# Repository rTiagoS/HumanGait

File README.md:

## "Classificação de Marcha Anômala utilizando técnicas de Machine Learning e Sensores Embarcados."

### Publicações

Para mais detalhes, verifique nosso artigo: https://arxiv.org/abs/2110.06139

Caso nosso dataset seja utilizado, por favor, nos cite utilizando a seguinte referência: &nbsp;
```
@misc{sa2021classification,
      title={Classification of anomalous gait using Machine Learning techniques and embedded sensors}, 
      author={T. R. D. Sa and C. M. S. Figueiredo},
      year={2021},
      eprint={2110.06139},
      archivePrefix={arXiv},
      primaryClass={eess.SP}
}
```

Link para o dataset: https://drive.google.com/drive/folders/1B0GRPU912k93h7YRrBrzX0vYdbw2wq_Z?usp=sharing

##### Este repositório, em síntese, viabiliza o acesso aos três módulos que implementam o projeto proposto. Os módulos são:

**1. Módulo da Aplicação Embarcada**;
   * Modelagem do esquemático e layout do hardware embarcado;
   * Integração do sensor MPU-6050 ao microcontrolador ESP32 DevKit C;
   * Integração dos dados coletados para um servidor Broker MQTT (Internet das Coisas);
  
  Tecnologias utilizadas:
   * Linguagens de programação C e C++ (implementação do software embarcado);
   * KiCAD para modelagem da PCB;
  
**2. Módulo da Aplicação Web**;
   * Implementação de uma interface para inserção de dados;
   * Integração ao ESP32 DevKit C e servidor Broker MQTT para testes de conexão;
   * Rotulação automática dos dados coletados para alimentar o dataset;
  
  Tecnologias utilizadas: 
  - Servidor Linux (Ubuntu 20.04) hospedando Node-RED e um servidor Broker MQTT Eclipse Mosquitto.
  
**3. Módulo da Aplicação IA**;
   * Implementação de diferentes modelos baseados em Machine Learning com a biblioteca scikit learn;
   * Implementação de diferentes modelos baseados em arquiteturas de Deep Learning com as bibliotecas Keras e Tensorflow;
  
  Tecnologias utilizadas:
   * Servidor Linux com GPU para treinamento de modelos de Deep Learning e Machine Learning;
   * Linguagem de programação Python para implementação dos modelos IA e rotinas de rotulagem automática do dataset;

 Para cada módulo, há um diretório com o respectivo nome de referência. Neles há os arquivos de implementação e entre outros detalhes.

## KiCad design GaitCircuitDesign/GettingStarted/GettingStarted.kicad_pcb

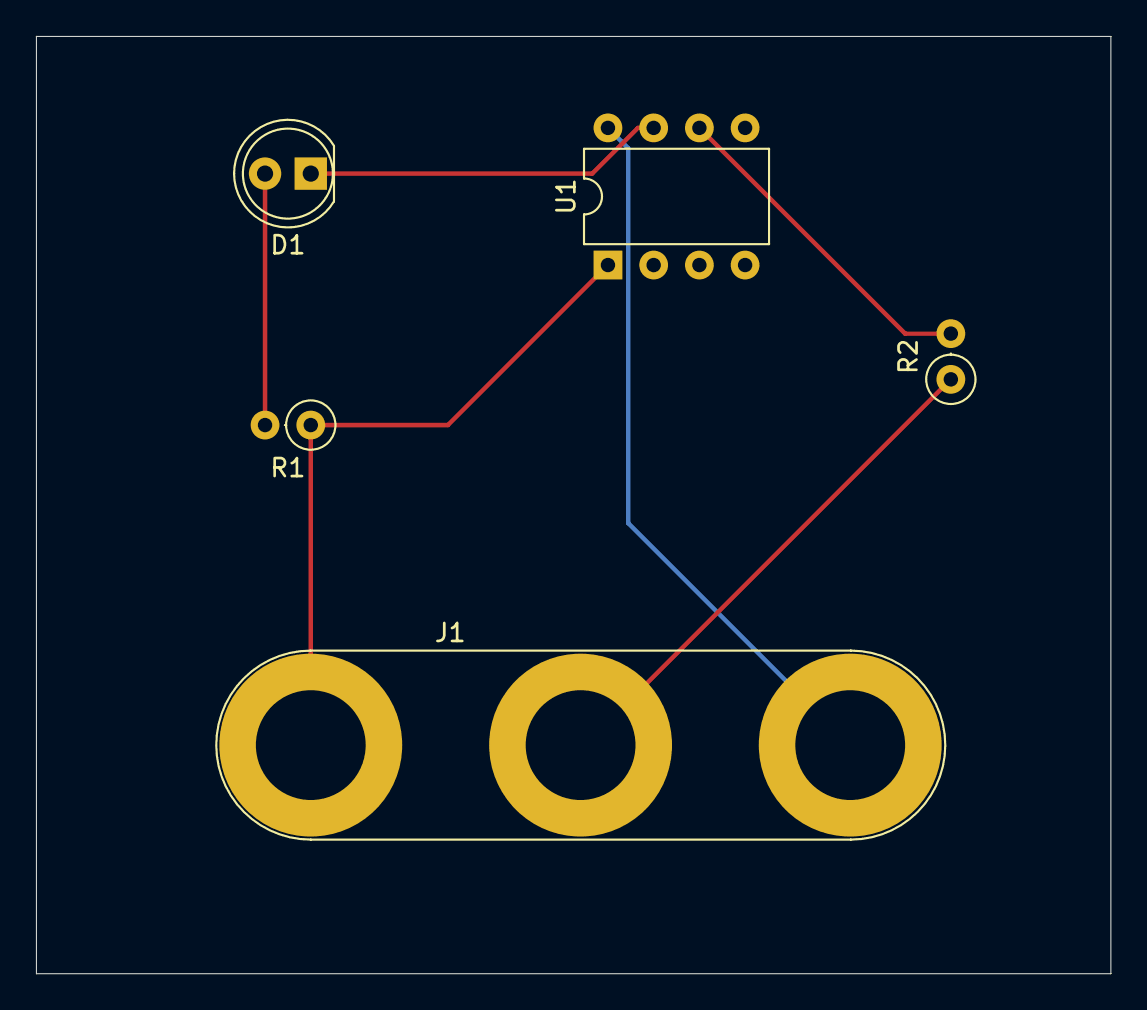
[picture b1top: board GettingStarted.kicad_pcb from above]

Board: 2 copper layers, 59.7 x 52.1 mm, 5 parts (0 on the bottom side), 6 nets.

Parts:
D1: LED; LED_D5.0mm
J1: MYCONN3; Banana_Jack_3Pin
R1: 1k; R_Axial_DIN0207_L6.3mm_D2.5mm_P2.54mm_Vertical
R2: 100; R_Axial_DIN0207_L6.3mm_D2.5mm_P2.54mm_Vertical
U1: PIC12C508A-ISN; DIP-8_W7.62mm

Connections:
/INPUT: R2.2, U1.6
/INPUTtoR: J1.2, R2.1
/LEDtoR: D1.2, R1.2
/uCtoLED: D1.1, U1.7
GND: J1.3, U1.8
VCC: J1.1, R1.1, U1.1

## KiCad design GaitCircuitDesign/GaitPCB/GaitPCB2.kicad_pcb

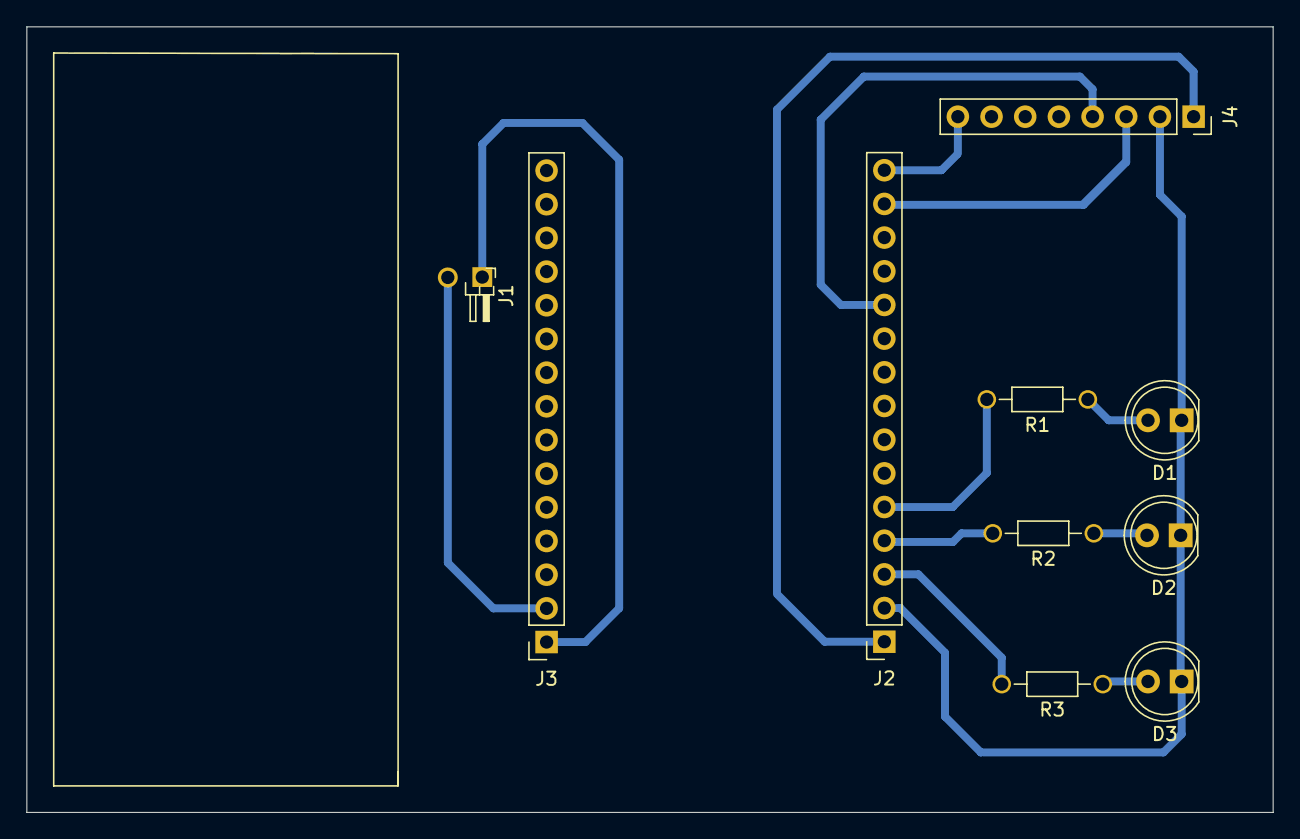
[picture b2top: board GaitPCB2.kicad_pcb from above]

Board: 2 copper layers, 94.0 x 59.2 mm, 10 parts (0 on the bottom side), 12 nets.

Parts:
D1, D2, D3: LED; LED_D5.0mm
J1: Conn_01x02_Male; PinHeader_1x02_P1.00mm_Horizontal
J2: Conn_01x15_Female_MPU; PinSocket_1x15_P2.54mm_Vertical
J3: Conn_01x15_Female; PinSocket_1x15_P2.54mm_Vertical
J4: Conn_01x08_Female; PinSocket_1x08_P2.54mm_Vertical
R1, R2, R3: R; R_Axial_DIN0204_L3.6mm_D1.6mm_P7.62mm_Horizontal

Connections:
+3V3: J2.1, J4.1
GND: D1.1, D2.1, D3.1, J1.2, J2.2, J3.2, J4.2
unnamed: D1.2, R1.1
unnamed: D2.2, R2.1
unnamed: D3.2, R3.1
unnamed: J2.3, R3.2
unnamed: J2.4, R2.2
unnamed: J2.5, R1.2
unnamed: J2.11, J4.4
unnamed: J2.14, J4.3
unnamed: J2.15, J4.8
VDD: J1.1, J3.1

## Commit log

2021-01-18 Criando repositório para o projeto. Criado .gitignore
2021-01-24 Modelo de Deep Learning com arquitetura simples criado. Atual acurácia: 93%, test_size = 0.2
2021-10-13 Deleting package-lock.json since it has security issues.
2021-10-13 Adding arvix reference
2021-10-13 Incluindo link para o dataset.
2021-10-13 Adjusting readme markdown
